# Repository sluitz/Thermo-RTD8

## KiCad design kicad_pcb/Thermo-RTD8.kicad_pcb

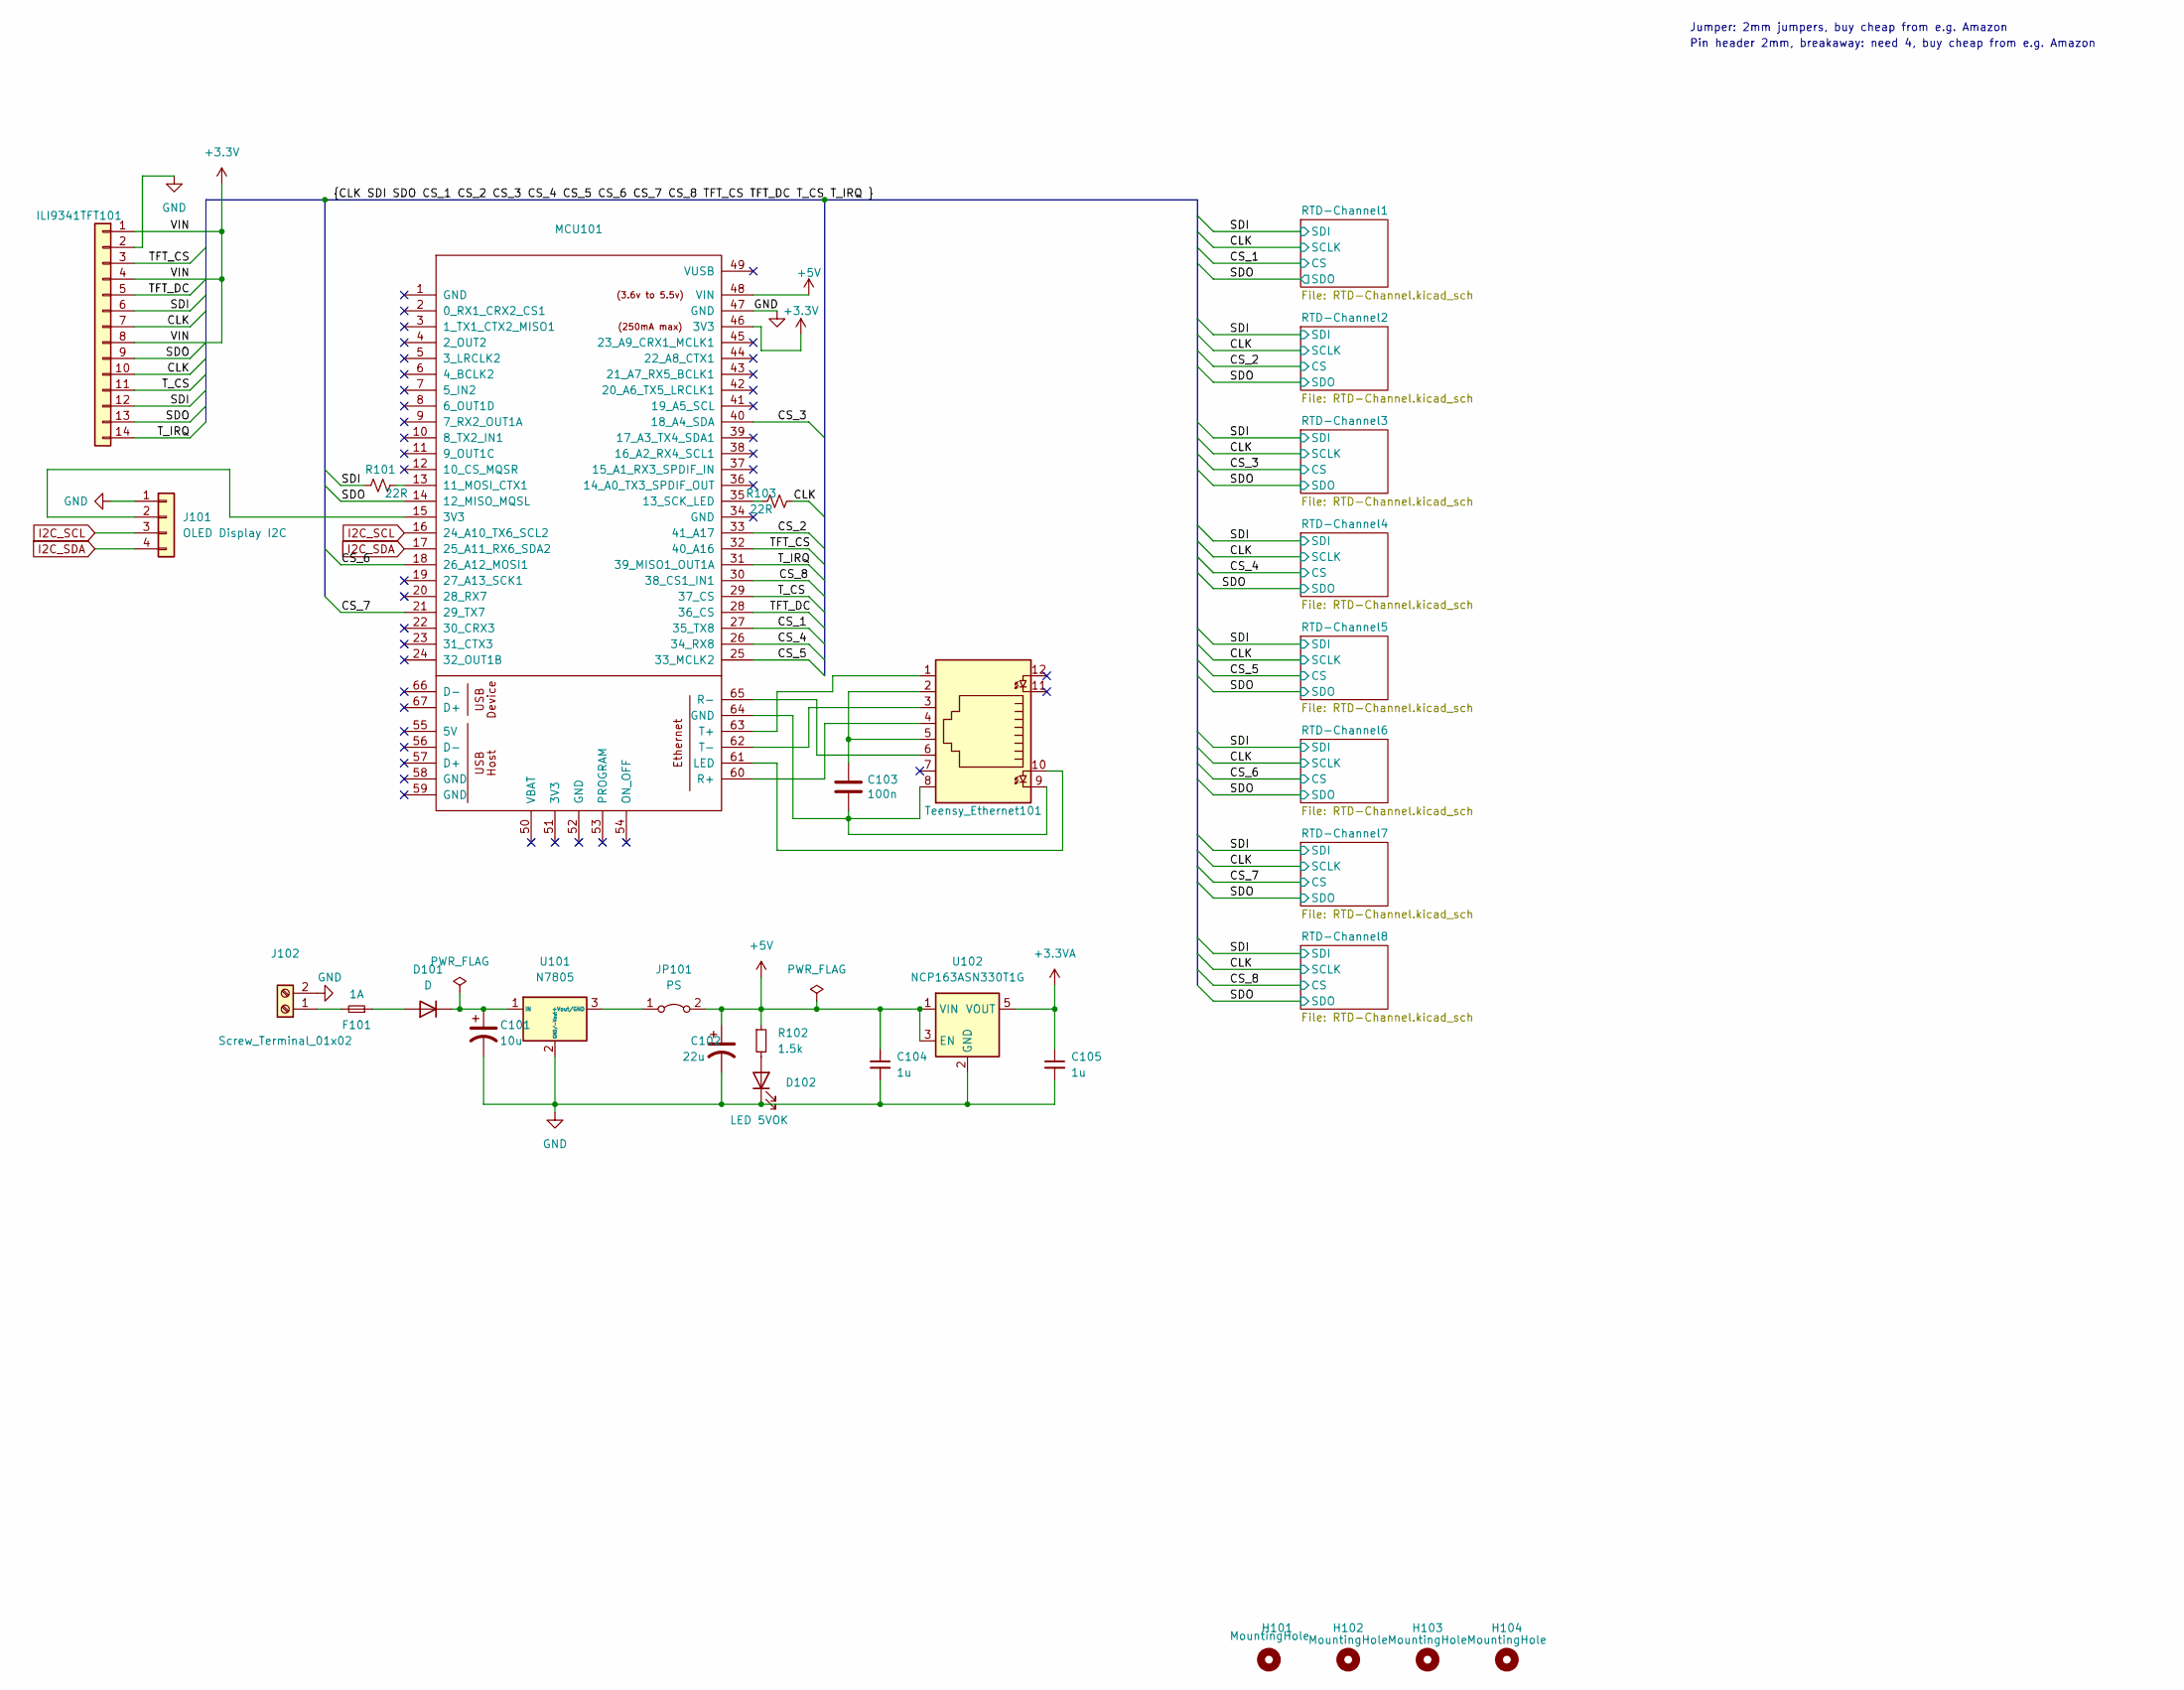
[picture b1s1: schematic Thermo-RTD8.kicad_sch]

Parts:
C101: 10u; CP_Radial_D5.0mm_P2.00mm
C102: 22u; CP_Radial_D5.0mm_P2.00mm
C103: 100n; C_0805_2012Metric_Pad1.18x1.45mm_HandSolder
C104, C105: 1u; C_0805_2012Metric_Pad1.18x1.45mm_HandSolder
D101: D; D_SOD-123
D102: LED 5VOK; LED_0805_2012Metric_Pad1.15x1.40mm_HandSolder
F101: 1A; smd_fuse
H101, H102, H103, H104: MountingHole; MountingHole_3.2mm_M3_DIN965
ILI9341TFT101: ILI9341TFT-RibbonCable
J101: OLED Display I2C; PinSocket_1x04_P2.54mm_Vertical
J102: Screw_Terminal_01x02; TB00750802BE
JP101: PS; PinHeader_1x02_P2.54mm_Vertical
MCU101: Teensy41
R101, R103: 22R; R_0805_2012Metric_Pad1.20x1.40mm_HandSolder
R102: 1.5k; R_0805_2012Metric_Pad1.20x1.40mm_HandSolder
Teensy_Ethernet101: RJ45_Cetus_J1B1211CCD_Horizontal
U101: N7805; N78051C
U102: NCP163ASN330T1G; SOT-23-5

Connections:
+3.3V: ILI9341TFT101.1, ILI9341TFT101.4, ILI9341TFT101.8, MCU101.46 (3V3); also elsewhere on the board
+3.3VA: C105.1, U102.5 (VOUT); also elsewhere on the board
+5V: C102.1, C104.1, JP101.2 (B), MCU101.48 (VIN), R102.1, U102.1 (VIN), U102.3 (EN)
/CLK: ILI9341TFT101.7, ILI9341TFT101.10, R103.1; also elsewhere on the board
/CS_1: MCU101.27 (35_TX8); also elsewhere on the board
/CS_2: MCU101.33 (41_A17); also elsewhere on the board
/CS_3: MCU101.40 (18_A4_SDA); also elsewhere on the board
/CS_4: MCU101.26 (34_RX8); also elsewhere on the board
/CS_5: MCU101.25 (33_MCLK2); also elsewhere on the board
/CS_6: MCU101.18 (26_A12_MOSI1); also elsewhere on the board
/CS_7: MCU101.21 (29_TX7); also elsewhere on the board
/CS_8: MCU101.30 (38_CS1_IN1); also elsewhere on the board
/SDI: ILI9341TFT101.6, ILI9341TFT101.12, R101.2; also elsewhere on the board
/SDO: ILI9341TFT101.9, ILI9341TFT101.13, MCU101.14 (12_MISO_MQSL); also elsewhere on the board
/TFT_CS: ILI9341TFT101.3, MCU101.32 (40_A16)
/TFT_DC: ILI9341TFT101.5, MCU101.28 (36_CS)
/T_CS: ILI9341TFT101.11, MCU101.29 (37_CS)
/T_IRQ: ILI9341TFT101.14, MCU101.31 (39_MISO1_OUT1A)
GND: C101.2, C102.2, C104.2, C105.2, D102.1 (K), ILI9341TFT101.2, J101.1, J102.2, MCU101.47 (GND), U101.2 (GND/-Vout), U102.2 (GND); also elsewhere on the board
I2C_SCL: J101.3, MCU101.16 (24_A10_TX6_SCL2)
I2C_SDA: J101.4, MCU101.17 (25_A11_RX6_SDA2)
unnamed: C103.1, Teensy_Ethernet101.2, Teensy_Ethernet101.5
unnamed: C103.2, MCU101.64 (GND), Teensy_Ethernet101.8, Teensy_Ethernet101.9
unnamed: D101.2 (A), F101.1
unnamed: C101.1, D101.1 (K), U101.1 (IN)
unnamed: D102.2 (A), R102.2
unnamed: J101.2, MCU101.15 (3V3)
unnamed: F101.2, J102.1
unnamed: JP101.1 (A), U101.3 (+Vout/GND)
unnamed: MCU101.13 (11_MOSI_CTX1), R101.1
unnamed: MCU101.35 (13_SCK_LED), R103.2
unnamed: MCU101.61 (LED), Teensy_Ethernet101.10
unnamed: MCU101.60 (R+), Teensy_Ethernet101.4
unnamed: MCU101.65 (R-), Teensy_Ethernet101.6
unnamed: MCU101.63 (T+), Teensy_Ethernet101.1
unnamed: MCU101.62 (T-), Teensy_Ethernet101.3

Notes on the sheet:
Pin header 2mm, breakaway: need 4, buy cheap from e.g. Amazon
Jumper: 2mm jumpers, buy cheap from e.g. Amazon

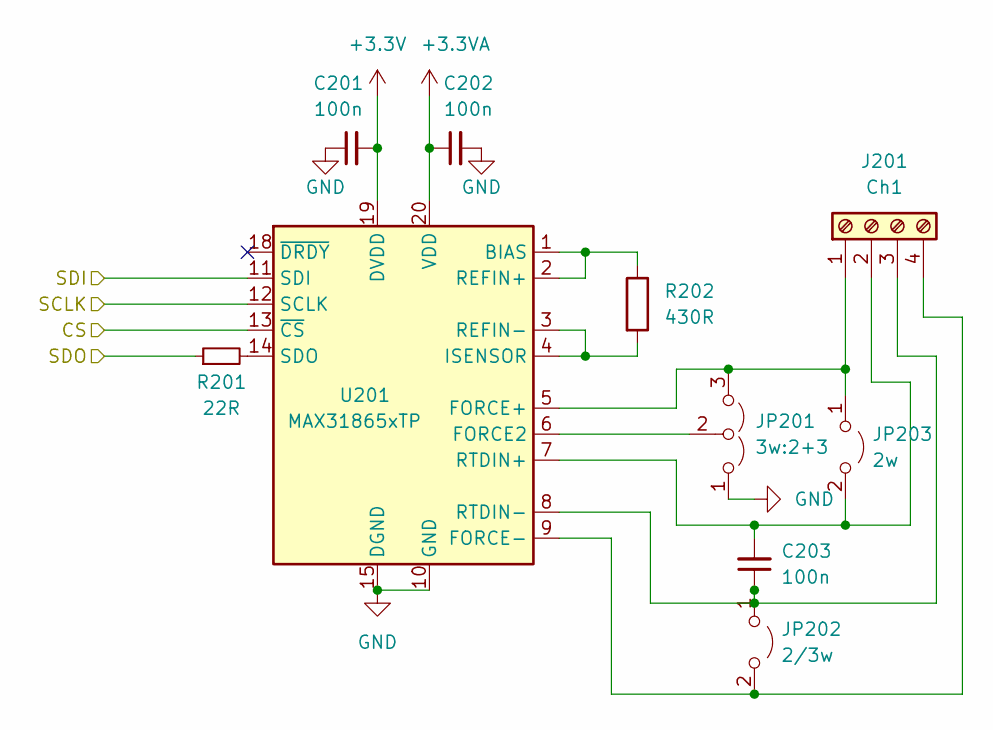
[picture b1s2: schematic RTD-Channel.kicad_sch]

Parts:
C201, C202, C203: 100n; C_0805_2012Metric_Pad1.18x1.45mm_HandSolder
J201: Ch1; TerminalBlock_Phoenix_PT-1,5-4-3.5-H_1x04_P3.50mm_Horizontal
JP201: 3w:2+3; PinHeader_1x03_P2.00mm_Vertical
JP202: 2/3w; PinHeader_1x02_P2.00mm_Vertical
JP203: 2w; PinHeader_1x02_P2.00mm_Vertical
R201: 22R; R_0805_2012Metric_Pad1.20x1.40mm_HandSolder
R202: 430R; R_0805_2012Metric_Pad1.20x1.40mm_HandSolder
U201: MAX31865xTP; TQFN-20-1EP_5x5mm_P0.65mm_EP3.25x3.25mm

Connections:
+3.3V: C201.2, U201.19 (DVDD); also elsewhere on the board
+3.3VA: C202.1, U201.20 (VDD); also elsewhere on the board
/CLK: U201.12 (SCLK); also elsewhere on the board
/CS_1: U201.13 (~CS); also elsewhere on the board
/SDI: U201.11 (SDI); also elsewhere on the board
/SDO: R201.1; also elsewhere on the board
GND: C201.1, C202.2, JP201.1 (A), U201.10 (GND), U201.15 (DGND), U201.16 (GND), U201.21 (GND); also elsewhere on the board
unnamed: J201.1, JP201.3 (B), JP203.1 (A), U201.5 (FORCE+)
unnamed: C203.2, J201.2, JP203.2 (B), U201.7 (RTDIN+)
unnamed: C203.1, J201.3, JP202.1 (A), U201.8 (RTDIN-)
unnamed: J201.4, JP202.2 (B), U201.9 (FORCE-)
unnamed: JP201.2 (C), U201.6 (FORCE2)
unnamed: R202.1, U201.1 (BIAS), U201.2 (REFIN+)
unnamed: R202.2, U201.3 (REFIN-), U201.4 (ISENSOR)
unnamed: R201.2, U201.14 (SDO)

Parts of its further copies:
C301, C302, C303, C401, C402, C403, C501, C502, C503, C601, C602, C603, C701, C702, C703, C801, C802, C803, C901, C902, C903: 100n; C_0805_2012Metric_Pad1.18x1.45mm_HandSolder
J301, J401, J501, J601, J701, J801, J901: Ch1; TerminalBlock_Phoenix_PT-1,5-4-3.5-H_1x04_P3.50mm_Horizontal
JP301, JP401, JP501, JP601, JP701, JP801, JP901: 3w:2+3; PinHeader_1x03_P2.00mm_Vertical
JP302, JP402, JP502, JP602, JP702, JP802, JP902: 2/3w; PinHeader_1x02_P2.00mm_Vertical
JP303, JP403, JP503, JP603, JP703, JP803, JP903: 2w; PinHeader_1x02_P2.00mm_Vertical
R301, R401, R501, R601, R701, R801, R901: 22R; R_0805_2012Metric_Pad1.20x1.40mm_HandSolder
U301, U401, U501, U601, U701, U801, U901: MAX31865xTP; TQFN-20-1EP_5x5mm_P0.65mm_EP3.25x3.25mm

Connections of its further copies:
+3.3V: C301.2, C401.2, C501.2, C601.2, C701.2, C801.2, C901.2, U301.19 (DVDD), U401.19 (DVDD), U501.19 (DVDD), U601.19 (DVDD), U701.19 (DVDD), U801.19 (DVDD), U901.19 (DVDD); also elsewhere on the board
+3.3VA: C302.1, C402.1, C502.1, C602.1, C702.1, C802.1, C902.1, U301.20 (VDD), U401.20 (VDD), U501.20 (VDD), U601.20 (VDD), U701.20 (VDD), U801.20 (VDD), U901.20 (VDD); also elsewhere on the board
/CLK: U301.12 (SCLK), U401.12 (SCLK), U501.12 (SCLK), U601.12 (SCLK), U701.12 (SCLK), U801.12 (SCLK), U901.12 (SCLK); also elsewhere on the board
/CS_2: U401.13 (~CS); also elsewhere on the board
/CS_3: U301.13 (~CS); also elsewhere on the board
/CS_4: U501.13 (~CS); also elsewhere on the board
/CS_5: U601.13 (~CS); also elsewhere on the board
/CS_6: U701.13 (~CS); also elsewhere on the board
/CS_7: U801.13 (~CS); also elsewhere on the board
/CS_8: U901.13 (~CS); also elsewhere on the board
/SDI: U301.11 (SDI), U401.11 (SDI), U501.11 (SDI), U601.11 (SDI), U701.11 (SDI), U801.11 (SDI), U901.11 (SDI); also elsewhere on the board
/SDO: R301.1, R401.1, R501.1, R601.1, R701.1, R801.1, R901.1; also elsewhere on the board
GND: C301.1, C302.2, C401.1, C402.2, C501.1, C502.2, C601.1, C602.2, C701.1, C702.2, C801.1, C802.2, C901.1, C902.2, JP301.1 (A), JP401.1 (A), JP501.1 (A), JP601.1 (A), JP701.1 (A), JP801.1 (A), JP901.1 (A), U301.10 (GND), U301.15 (DGND), U301.16 (GND), U301.21 (GND), U401.10 (GND), U401.15 (DGND), U401.16 (GND), U401.21 (GND), U501.10 (GND), U501.15 (DGND), U501.16 (GND), U501.21 (GND), U601.10 (GND), U601.15 (DGND), U601.16 (GND), U601.21 (GND), U701.10 (GND), U701.15 (DGND), U701.16 (GND), U701.21 (GND), U801.10 (GND), U801.15 (DGND), U801.16 (GND), U801.21 (GND), U901.10 (GND), U901.15 (DGND), U901.16 (GND), U901.21 (GND); also elsewhere on the board
unnamed: J301.1, JP301.3 (B), JP303.1 (A), U301.5 (FORCE+)
unnamed: C303.2, J301.2, JP303.2 (B), U301.7 (RTDIN+)
unnamed: C303.1, J301.3, JP302.1 (A), U301.8 (RTDIN-)
unnamed: J301.4, JP302.2 (B), U301.9 (FORCE-)
unnamed: J401.1, JP401.3 (B), JP403.1 (A), U401.5 (FORCE+)
unnamed: C403.2, J401.2, JP403.2 (B), U401.7 (RTDIN+)
unnamed: C403.1, J401.3, JP402.1 (A), U401.8 (RTDIN-)
unnamed: J401.4, JP402.2 (B), U401.9 (FORCE-)
unnamed: J501.1, JP501.3 (B), JP503.1 (A), U501.5 (FORCE+)
unnamed: C503.2, J501.2, JP503.2 (B), U501.7 (RTDIN+)
unnamed: C503.1, J501.3, JP502.1 (A), U501.8 (RTDIN-)
unnamed: J501.4, JP502.2 (B), U501.9 (FORCE-)
unnamed: J601.1, JP601.3 (B), JP603.1 (A), U601.5 (FORCE+)
unnamed: C603.2, J601.2, JP603.2 (B), U601.7 (RTDIN+)
unnamed: C603.1, J601.3, JP602.1 (A), U601.8 (RTDIN-)
unnamed: J601.4, JP602.2 (B), U601.9 (FORCE-)
unnamed: J701.1, JP701.3 (B), JP703.1 (A), U701.5 (FORCE+)
unnamed: C703.2, J701.2, JP703.2 (B), U701.7 (RTDIN+)
unnamed: C703.1, J701.3, JP702.1 (A), U701.8 (RTDIN-)
unnamed: J701.4, JP702.2 (B), U701.9 (FORCE-)
unnamed: J801.1, JP801.3 (B), JP803.1 (A), U801.5 (FORCE+)
unnamed: C803.2, J801.2, JP803.2 (B), U801.7 (RTDIN+)
unnamed: C803.1, J801.3, JP802.1 (A), U801.8 (RTDIN-)
unnamed: J801.4, JP802.2 (B), U801.9 (FORCE-)
unnamed: J901.1, JP901.3 (B), JP903.1 (A), U901.5 (FORCE+)
unnamed: C903.2, J901.2, JP903.2 (B), U901.7 (RTDIN+)
unnamed: C903.1, J901.3, JP902.1 (A), U901.8 (RTDIN-)
unnamed: J901.4, JP902.2 (B), U901.9 (FORCE-)
unnamed: JP301.2 (C), U301.6 (FORCE2)
unnamed: JP401.2 (C), U401.6 (FORCE2)
unnamed: JP501.2 (C), U501.6 (FORCE2)
unnamed: JP601.2 (C), U601.6 (FORCE2)
unnamed: JP701.2 (C), U701.6 (FORCE2)
unnamed: JP801.2 (C), U801.6 (FORCE2)
unnamed: JP901.2 (C), U901.6 (FORCE2)
unnamed 79: U301.1 (BIAS), U301.2 (REFIN+); also elsewhere on the board
unnamed 80: U301.3 (REFIN-), U301.4 (ISENSOR); also elsewhere on the board
unnamed: R301.2, U301.14 (SDO)
unnamed 82: U401.1 (BIAS), U401.2 (REFIN+); also elsewhere on the board
unnamed 83: U401.3 (REFIN-), U401.4 (ISENSOR); also elsewhere on the board
unnamed: R401.2, U401.14 (SDO)
unnamed 85: U501.1 (BIAS), U501.2 (REFIN+); also elsewhere on the board
unnamed 86: U501.3 (REFIN-), U501.4 (ISENSOR); also elsewhere on the board
unnamed: R501.2, U501.14 (SDO)
unnamed 88: U601.1 (BIAS), U601.2 (REFIN+); also elsewhere on the board
unnamed 89: U601.3 (REFIN-), U601.4 (ISENSOR); also elsewhere on the board
unnamed: R601.2, U601.14 (SDO)
unnamed 91: U701.1 (BIAS), U701.2 (REFIN+); also elsewhere on the board
unnamed 92: U701.3 (REFIN-), U701.4 (ISENSOR); also elsewhere on the board
unnamed: R701.2, U701.14 (SDO)
unnamed 94: U801.1 (BIAS), U801.2 (REFIN+); also elsewhere on the board
unnamed 95: U801.3 (REFIN-), U801.4 (ISENSOR); also elsewhere on the board
unnamed: R801.2, U801.14 (SDO)
unnamed 97: U901.1 (BIAS), U901.2 (REFIN+); also elsewhere on the board
unnamed 98: U901.3 (REFIN-), U901.4 (ISENSOR); also elsewhere on the board
unnamed: R901.2, U901.14 (SDO)

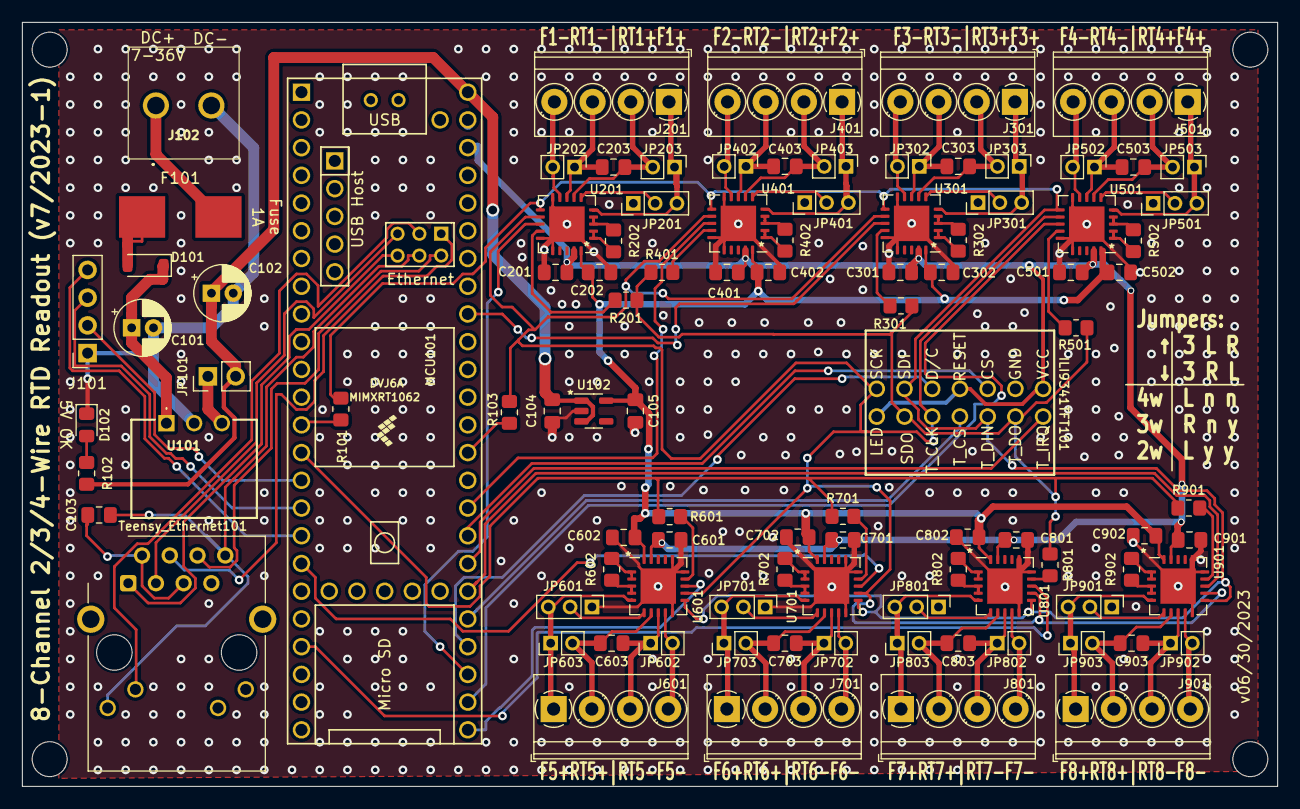
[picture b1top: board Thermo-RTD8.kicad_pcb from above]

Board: 2 copper layers, 115.0 x 70.0 mm, 103 parts (0 on the bottom side), 100 nets.

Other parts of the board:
R302, R402, R502, R602, R702, R802, R902: 440R; R_0805_2012Metric_Pad1.20x1.40mm_HandSolder

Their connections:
unnamed 79: R302.1; also elsewhere on the board
unnamed 80: R302.2; also elsewhere on the board
unnamed 82: R402.1; also elsewhere on the board
unnamed 83: R402.2; also elsewhere on the board
unnamed 85: R502.1; also elsewhere on the board
unnamed 86: R502.2; also elsewhere on the board
unnamed 88: R602.1; also elsewhere on the board
unnamed 89: R602.2; also elsewhere on the board
unnamed 91: R702.1; also elsewhere on the board
unnamed 92: R702.2; also elsewhere on the board
unnamed 94: R802.1; also elsewhere on the board
unnamed 95: R802.2; also elsewhere on the board
unnamed 97: R902.1; also elsewhere on the board
unnamed 98: R902.2; also elsewhere on the board

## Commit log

2023-08-03 Thermo-RTD8 First commit
